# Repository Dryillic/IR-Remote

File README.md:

# IR-Remote

This repository has all the documentation, design and process in creating an IR remote
for a Dynex television using the NEC protocol and an ATtiny85 microcontroller. The goal 
is to create a maximum range IR remote for my girlfriends' TV that will be reliable, easy to use, 
have long battery life and look/work functionally equivilent to a regular TV remote.

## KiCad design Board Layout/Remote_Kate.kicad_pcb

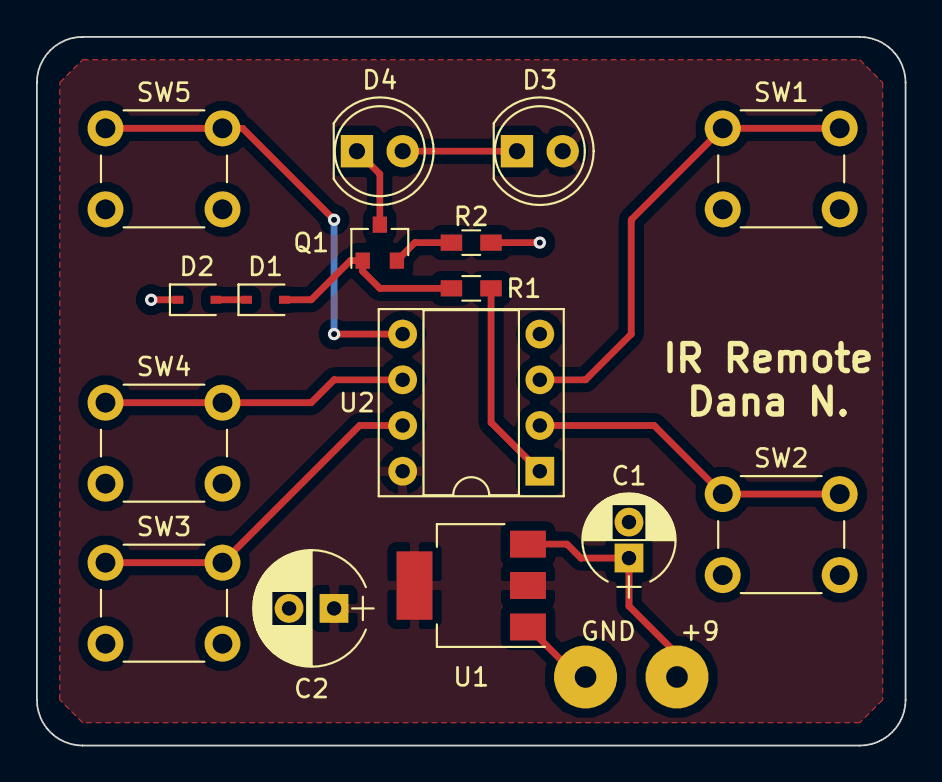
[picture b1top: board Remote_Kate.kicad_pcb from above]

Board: 2 copper layers, 48.3 x 39.4 mm, 18 parts (0 on the bottom side), 14 nets.

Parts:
+9: Conn_01x01; SolderWirePad_single_1-2mmDrill
C1: 10u; CP_Radial_D5.0mm_P2.00mm
C2: 100u; CP_Radial_D6.3mm_P2.50mm
D1, D2: D; D_SOD-323
D3, D4: LED; LED_D5.0mm
GND: Conn_01x01; SolderWirePad_single_1-2mmDrill
Q1: BC817-40; SOT-23
R1: 3.3k; R_0603_HandSoldering
R2: 1.5; R_0603_HandSoldering
SW1: Input; SW_PUSH_6mm_h13mm
SW2: Mute; SW_PUSH_6mm_h13mm
SW3: Vol_Down; SW_PUSH_6mm_h13mm
SW4: Vol_Up; SW_PUSH_6mm_h13mm
SW5: Power; SW_PUSH_6mm_h13mm
U1: AP1117; SOT-223-3_TabPin2
U2: ATTINY85-20PU; DIP-8_W7.62mm_Socket

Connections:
5V_REF: C2.1, D3.2, U1.2, U2.8
9V_PWR: +9.1, C1.1, U1.3
GND: C1.2, C2.2, D2.1, GND.1, R2.2, SW1.2, SW2.2, SW3.2, SW4.2, SW5.2, U1.1, U2.4
unnamed: D1.1, D2.2
unnamed: D1.2, Q1.1, R1.2
unnamed: D3.1, D4.2
unnamed: D4.1, Q1.3
unnamed: Q1.2, R2.1
unnamed: SW1.1, U2.3
unnamed: SW2.1, U2.2
unnamed: SW3.1, U2.7
unnamed: SW4.1, U2.6
unnamed: SW5.1, U2.5
PINX_MCIN: R1.1, U2.1

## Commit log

2017-10-17 :lollipop: Added .gitattributes & .gitignore files
2017-10-17 File System
    Added main c code and folder system.
2017-10-17 Parts
    Updated order list with new components.
2017-10-17 Board Design
    Added board design schematic and layout. Subject to change, further work
    required to send to fab.
2017-10-17 Update 10.16.17
    -Changed micro controller to more compact ATtiny85
2017-10-17 Updated 10.16.17
    Added Spice files and logs.
